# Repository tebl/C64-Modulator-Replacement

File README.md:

# C64 Modulator replacement ("Longboard" edition)

Based on the C64 RF-modulator mod by [Zero-X / OMS](https://github.com/tebl/C64-Modulator-Replacement/raw/master/gallery/modulator_simple.png), this adapts those schematics to create a complete replacement for the original modulator including a few changes of my own. A nice writeup and the my original inspiration for making this version if it came from a blog post on [My Diy Blog](https://amazingdiy.wordpress.com/2013/02/08/c64-s-video-mod/) (not actually my blog, it's just called that).

The modulator replacement replaces the original circuit, with the original responsible for boosting the output from the VIC-chip and generating composite video, S-Video and the RF-signal. The replacement removes the old RF-signal output as well as the noise it provides, also added to it is options for bypassing some of the more problematic signals and a connector for adding stereo audio output. S-Video picture quality can be further improved upon by not installing the components for composite video.

Given differences in pinouts and voltages found on various Commodore 64 revisions, this variant is only meant for installation on Commodore 64s with so-called "longboards" only!

## Building the board
Soldering together the few components should be easy going as long as you have access to reasonable tools, personally I'm using a cheap soldering station with adjustable temperature so no need to go expensive if you don't have to. Use 60/40 soldering tin, the lead free kind makes the job a lot harder if you're new to the hobby.

Start by studying the PCB, both sides and perform dry fits where needed so that you have an idea of where everything should go since removing components is always a lot harder than getting it right in the first place. In particular, take care when it comes to the orientation of polarized components such as the electrolytic capacitors and diodes (match orientation to symbols, study the gallery images for reference). Perhaps the most important part is that since this board will be mounted on the C64-mainboard, there is large sections of exposed ground planes directly beneath where the modulator goes - you'll need to make sure nothing'll short between this part and the modulator replacement above, so cut leads short.

I recommend the following sequence when soldering the board together:
1. Check errata below for relevant changes
2. Decide if you want composite video, if not - identify components that do not need installing (see underside of board)
2. Resistors, diodes, inductors and non-polarized capacitors.
3. 7805 regulator
4. Transistors
5. Connectors (if needed)
6. See installing the board for the continuation, board alignment etc...

### Errata
- Revision B has bypass capacitors marked C8/C9, these are not necessary as they are already on the motherboard and the Stereo SID board. Having them there changes the sound experience somewhat, either leave them in place or replace them with a piece of wire.

## Installing the board
The first part of installing the board in a Commodore 64 with a longboard is removing the old regulator, this is a crucial step and is only recommended for people with experience working on antique hardware boards and have suitable equipment for doing so (excess heat over time = broken PCB). Free up the tabs holding the regulator, these are usually bent at an angle to grip and then soldered in place so you'll have to remove the solder and bend them back. Desolder the signal wires, two sections of four pins going into the modulator from the underside. Carefully probe each piece to ensure that it is loose before attempting to remove the modulator completely - impatience means broken traces!

With the old modulator removed, inspect the input pins to make sure that they're all still there and coninuity is sufficiently there before doing anything else. At this point in development you wouldn't want to subject the PCB to any more heat as it's already taken a lot, so what I recommend is installing male pin headers on the various connecting sections on the motherboard. Use the modulator replacement as a way of lining it all up, but only solder the male pins on the underside of the motherboard! Finally, remove modulator replacement and put some female headers on top of the pin headers just installed - put modulator replacement on top of those and solder in place just to get the alignment correct.

You should now have a modulator that can easily be removed from the machine if needed, that way you can easily upgrade to a later version of the module without taking the soldering iron to the C64 motherboard and quite possibly adjust the values to suit the picture if need be.

When connecting the board to the computer without any other hardware, you'd need to jumper across the two headers named LUM and CHR to connect the input signals to the motherboard. On most machines I've tried it with you'll get heavy jailbars on the screen, this is what the signal looks like coming into the modulator without the fuzzyness/smoothing added by the old one. This is where a board such as a Lumafix comes into the picture, it attempts to counteract the noise by adding some of it's own and smooth the signal somewhat (in essence, noise-cancelling instead of using a cleaner source). I've added a secondary connector at the top of my own [Lumafix-board](https://github.com/tebl/C64-Lumafix), this allows you to run the LUM and CHR signals directly from the VIC instead of running them across the motherboard.

Pictures below are taken from my system using composite cables from [RetroComputerShack](https://retrocomputershack.com/), some moire patterns appear due to me taking a picture of the LCD-screen using a mobile phone.

# Schematic
The supplied KiCad files should be sufficient as both a schematic and as a  starting point for ordering PCBs (basically you could just zip the contents of the export folder and upload that on a fabrication site), the schematic is also available in [PDF-format](https://github.com/tebl/C64-Modulator-Replacement/raw/master/export/C64%20Modulator.pdf) and this is what you'll need to print and work your way through this things don't work as expected after assembly. The original schematic by 

# BOM
Most parts should be easy to get a hold of from your favourite local electronic component shop, but given that I don't have access to such shops where I live so everything was based on whatever I could get cheapest from ebay/AliExpress (free shipping, plan on usually waiting 3-4 weeks though). The list below should be everything you'll need in addition to a workable soldering iron and some 60/40 soldering tin.

Pin headers you order in bulk and snap off parts as needed, relevant part details should also be present on the PCB itself for easy reference while assembling. Some components have been put in parenthesis, C2/C3 provide extra filtering while the rest is for adding composite output.

| Reference     | Item                                  | Count |
| ------------- | ------------------------------------- | ----- |
| PCB           | Fabricate using Gerber files          |     1 |
| C1            | 330pF capacitor                       |     1 |
| C3            | 330pF capacitor                       |    (1)|
| D1,D2         | 1N4148 small signal diode             |     2 |
| C2            | 150pF capacitor                       |    (1)|
| C4            | 10uF electrolytic capacitor (16v)     |     1 |
| C5            | 100uF electrolytic capacitor (16v)    |     1 |
| C6            | 68pF capacitor                        |    (1)|
| C7            | 100nF capacitor                       |     1 |
| L1            | 22uH axial inductor                   |     1 |
| L2            | 10uF axial inductor                   |    (1)|
| Q1-Q2         | BC549 transistor (TO-92)              |     2 |
| R1            | 1k ohm resistor                       |     1 | 
| R2            | 3k3 ohm resistor                      |     1 | 
| R3            | 5k6 ohm resistor                      |     1 | 
| R4            | 68 ohm resistor                       |     1 | 
| R5            | 220 ohm resistor                      |     1 | 
| R6            | 470 ohm resistor                      |     1 | 
| R7,R12        | 150 ohm resistor                      |     2 | 
| R8,R11        | 150 ohm resistor                      |    (2)| 
| U1            | LM7805 (TO-220)                       |     1 |
|               | Male header pins (break to size)      |     1 |
|               | 2pin female header*                   |     2 |
| J2,J3         | 4pin female header                    |     2 |
| J5 Audio      | 3.5mm 5pin green audio socket (PJ307) |    (1)|

\* Usually 1pin male pin header is soldered to ground points on the outer edges, usually a 1pin female header would be impractical so I use a 2pin or more female header with the rest of the pins pulled out.

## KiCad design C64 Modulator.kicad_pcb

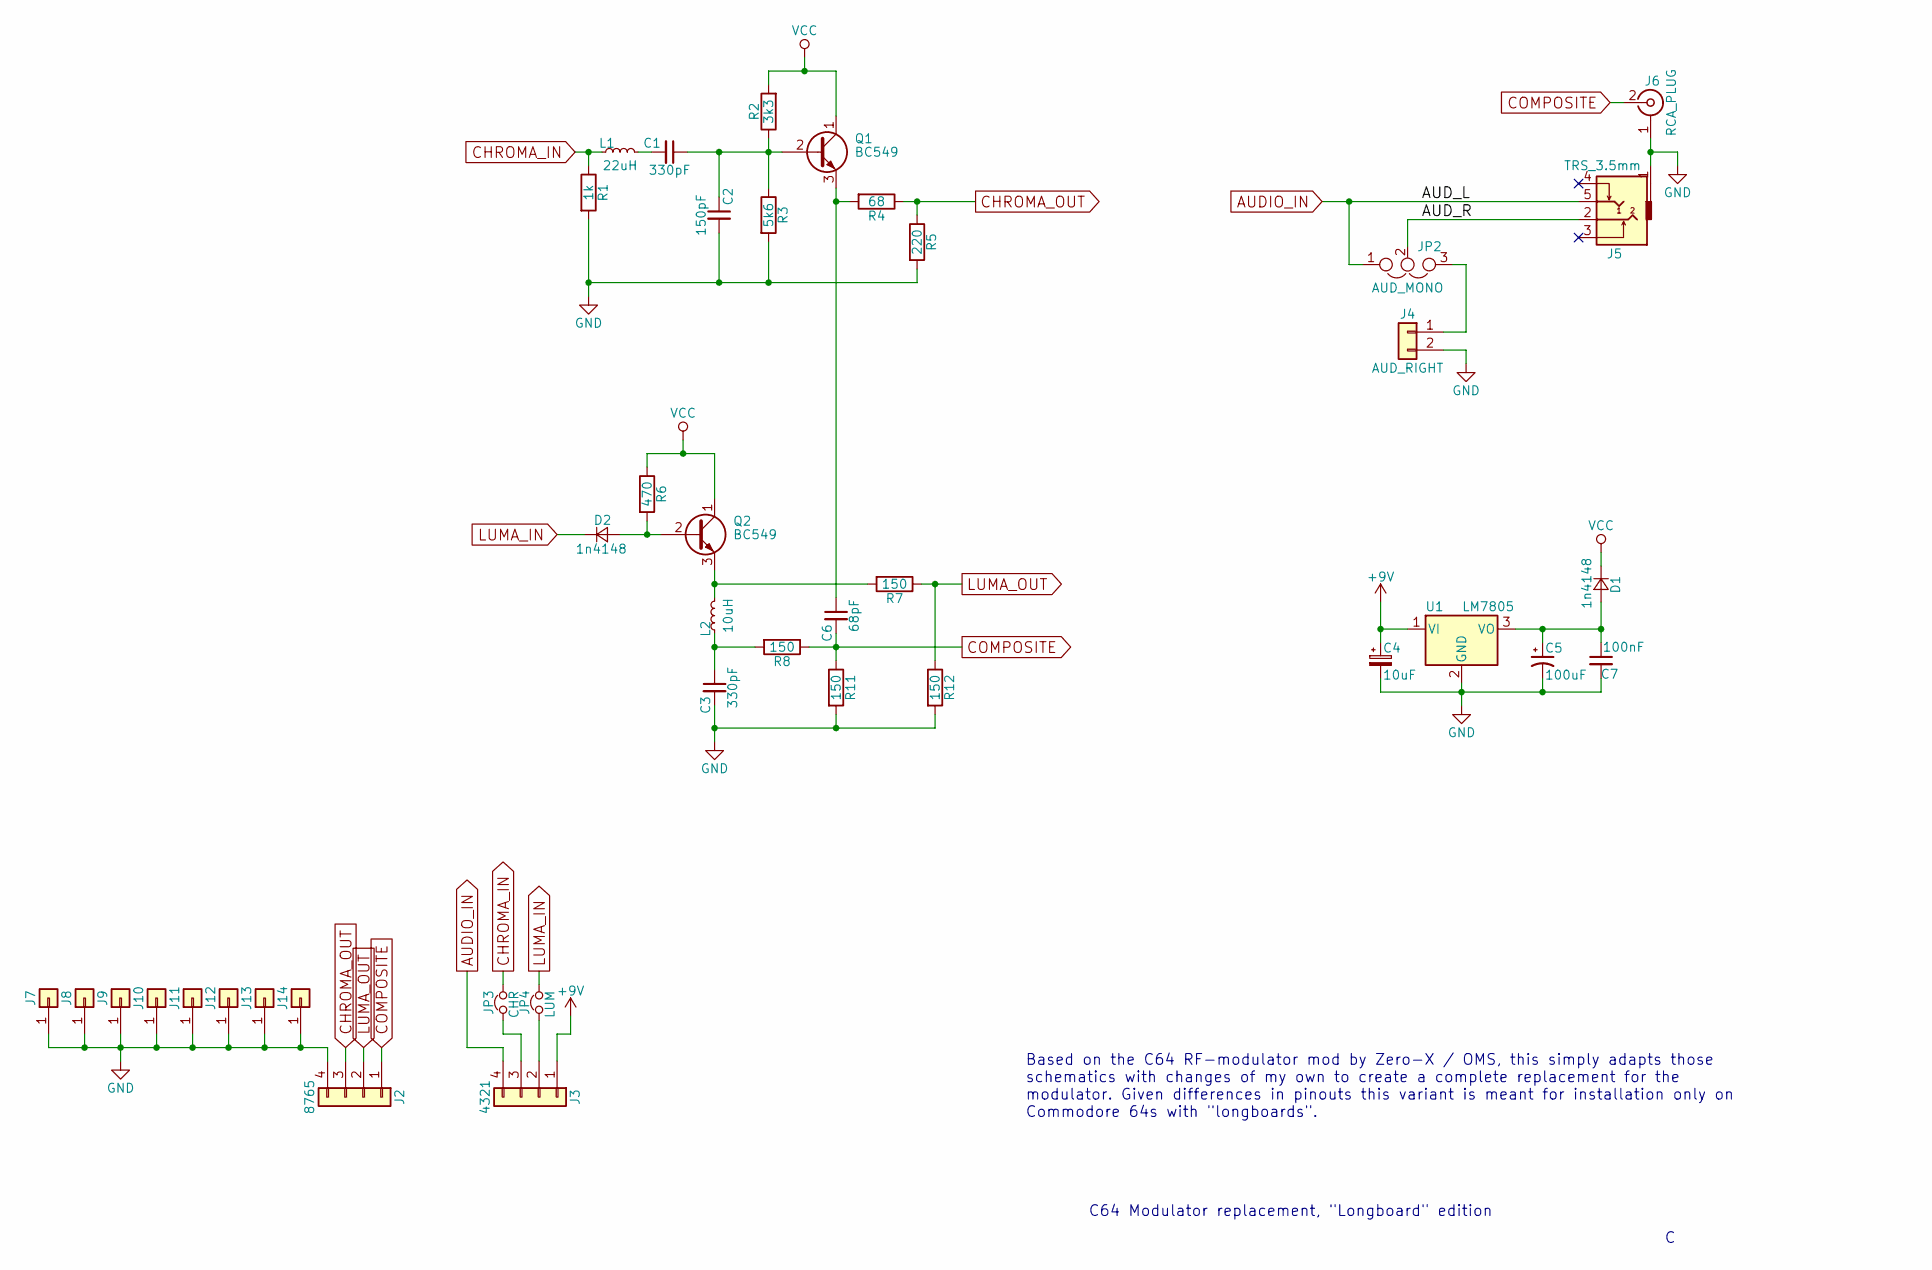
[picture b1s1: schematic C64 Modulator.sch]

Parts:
C1, C3: 330pF; C_Disc_D4.7mm_W2.5mm_P5.00mm
C2: 150pF; C_Disc_D4.7mm_W2.5mm_P5.00mm
C4: 10uF; CP_Radial_D5.0mm_P2.50mm
C5: 100uF; CP_Radial_D5.0mm_P2.50mm
C6: 68pF; C_Disc_D4.7mm_W2.5mm_P5.00mm
C7: 100nF; C_Disc_D4.7mm_W2.5mm_P5.00mm
D1, D2: 1n4148; D_DO-35_SOD27_P7.62mm_Horizontal
J2: 8765; Pin_Header_Straight_1x04_Pitch2.54mm
J3: 4321; Pin_Header_Straight_1x04_Pitch2.54mm
J4: AUD_RIGHT; Pin_Header_Straight_1x02_Pitch2.54mm
J5: TRS_3.5mm; Tayda_3.5mm_stereo_TRS_jack_A-853
J6: RCA_PLUG; rca_yellow
J7, J8, J9, J10, J11, J12, J13, J14: anchor_circle
JP2: AUD_MONO; Pin_Header_Straight_1x03_Pitch2.54mm
JP3: CHR; Pin_Header_Straight_1x02_Pitch2.54mm
JP4: LUM; Pin_Header_Straight_1x02_Pitch2.54mm
L1: 22uH; L_Axial_L6.6mm_D2.7mm_P10.16mm_Horizontal_Vishay_IM-2
L2: 10uH; L_Axial_L6.6mm_D2.7mm_P10.16mm_Horizontal_Vishay_IM-2
Q1, Q2: BC549; TO-92_Inline_Wide
R1: 1k; R_Axial_DIN0207_L6.3mm_D2.5mm_P10.16mm_Horizontal
R2: 3k3; R_Axial_DIN0207_L6.3mm_D2.5mm_P10.16mm_Horizontal
R3: 5k6; R_Axial_DIN0207_L6.3mm_D2.5mm_P10.16mm_Horizontal
R4: 68; R_Axial_DIN0207_L6.3mm_D2.5mm_P10.16mm_Horizontal
R5: 220; R_Axial_DIN0207_L6.3mm_D2.5mm_P10.16mm_Horizontal
R6: 470; R_Axial_DIN0207_L6.3mm_D2.5mm_P10.16mm_Horizontal
R7, R8, R11, R12: 150; R_Axial_DIN0207_L6.3mm_D2.5mm_P10.16mm_Horizontal
U1: LM7805; TO-220-3_Horizontal

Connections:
+9V: C4.1, J3.1, U1.1 (VI)
/AUD_R: J5.2, JP2.2
AUDIO_IN: J3.4, J5.5, JP2.1
CHROMA_IN: JP3.1, L1.1, R1.1
CHROMA_OUT: J2.3, R4.1, R5.1
COMPOSITE: C6.2, J2.1, J6.2 (In), R8.1, R11.1
GND: C2.2, C3.2, C4.2, C5.2, C7.2, J2.4, J4.2, J5.1, J6.1 (Ext), J7.1, J8.1, J9.1, J10.1, J11.1, J12.1, J13.1, J14.1, R1.2, R3.2, R5.2, R11.2, R12.2, U1.2 (GND)
LUMA_IN: D2.1 (K), JP4.1
LUMA_OUT: J2.2, R7.1, R12.1
unnamed: C1.1, C2.1, Q1.2 (B), R2.1, R3.1
unnamed: C1.2, L1.2
unnamed: C3.1, L2.1, R8.2
unnamed: C5.1, C7.1, D1.2 (A), U1.3 (VO)
unnamed: C6.1, Q1.3 (E), R4.2
unnamed: D2.2 (A), Q2.2 (B), R6.2
unnamed: J3.2, JP4.2
unnamed: J3.3, JP3.2
unnamed: J4.1, JP2.3
unnamed: L2.2, Q2.3 (E), R7.2
VCC: D1.1 (K), Q1.1 (C), Q2.1 (C), R2.2, R6.1

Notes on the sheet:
Based on the C64 RF-modulator mod by Zero-X / OMS, this simply adapts those schematics with changes of my own to create a complete replacement for the modulator. Given differences in pinouts this variant is meant for installation only on Commodore 64s with "longboards".
C64 Modulator replacement, "Longboard" edition

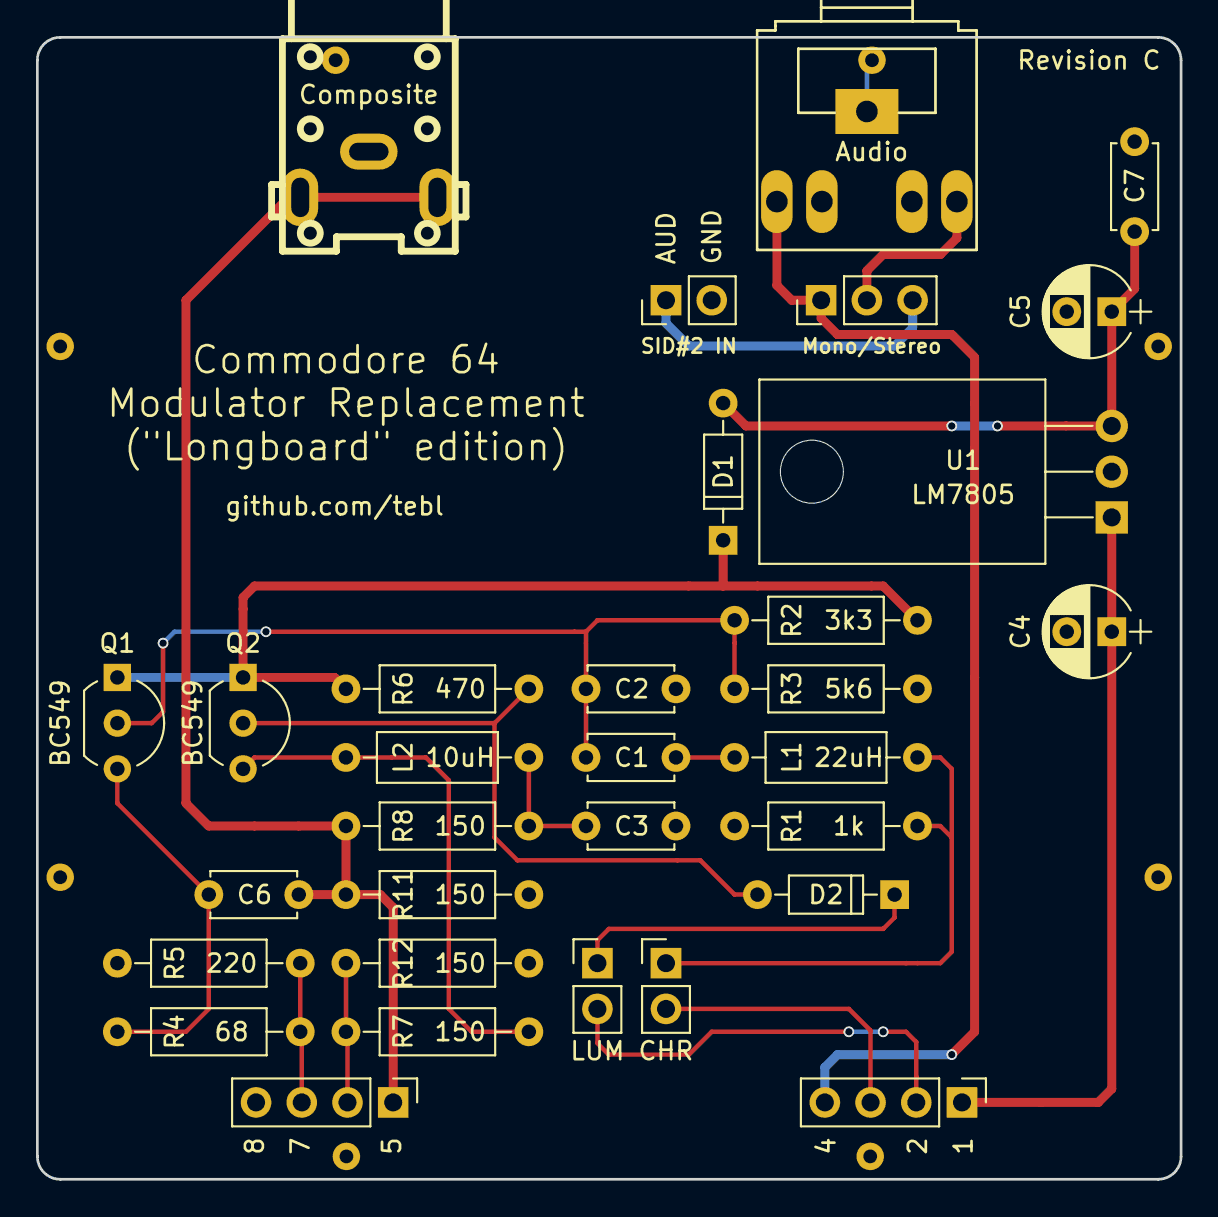
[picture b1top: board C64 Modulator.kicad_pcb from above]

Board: 2 copper layers, 63.5 x 63.4 mm, 40 parts (0 on the bottom side), 20 nets.

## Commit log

2019-06-21 Added schematic
2019-06-21 Assigned footprints
2019-06-26 Layout and silkscreen done
2019-06-26 Gerber export
2019-06-26 Added component notices to PCB
2019-08-08 Added 5v regulator to board
2019-08-08 Added symbols used
2019-08-08 Readded D1
2019-08-15 Audio decoupling caps on schematic
2019-08-17 Assigned updated footprints
2019-08-17 Updated PCB layout
2019-08-17 Added README blurb
2019-10-18 Updated gallery
2019-10-18 Resized image
2019-10-18 Removed C8/C9
2019-11-08 Updated gerbers
